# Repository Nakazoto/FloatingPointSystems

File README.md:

# Floating Point Systems

A repository for gathering documentation and understanding Floating-Point-Systems machines.

> [!NOTE]
> This documentation is incomplete and will be expanded as more information becomes available.

> [!WARNING]
> This README needs to be verified by the REPO owner: Nakazoto. 

## Overview

This project contains datasheets, documentation, and code related to floating-point-sytems machines.

## Index - For README

1. [Overview](#overview) - Reason What this REPO is for. 
2. [Contents](#contents---of-each-folder) - What is in the Folders.
3. [Index for FPS](#index---for-the-folders) - Folder links.
4. [Contributing](#contributing) - Things to look out for.
    - [Guide on Contributing](#a-little-guide) - A guide on contributing.

## Contents - Of each folder

- Documentation on floating-point-systems
- Some Datasheets
- Photos of Cards, etc
- Code for the Machines

## Index - For the folders

1. 	[OLD](!Old/) - Folder with old stuff , _A trade of some sort_
2. 	[AP 120B](AP%20120B/) - Documentation folder for AP 120B, _the predecessor of the FPS 100._
3. 	[FPS 100](FPS%20100/) - Documentation folder for FPS 100, _the successor of the AP 120B. With reduced cards._
4.	[FPS 164](FPS%20164/) - Documentation folder for FPS 164, _the favorite machine of Usagi Electric._
5. 	[FPS 3000](FPS%203000/) - Documentation folder for FPS 3000, _the machine of which only 1 still known to exist. And is almost the same as the XP 32 is._
6.	[FPS 5000](FPS%205000/) - Documentation folder for FPS 5000, _As mentioned in fps.pdf, this is a family of the AP 120B, just like any other machine._
7. 	[Random FPS information](Z.%20Others/) - Documetation folder for FPS information, _Like part prices and boardrevisions._
8. 	[Random PDFs](Z_Brochures/) - Documentation folder for PDFs, _Like product pages and folders._
9. 	[Boards in FPS Machines](Cully_Dave.txt) - Documentation file for cards, _The card configuration on different machines._
10. [Magazine of some sort](Digital_Design_V12_N06_198206.pdf) - Some sort of Magazine.
11. [Boards](FPS%20Board%20List.txt) - A board series, _with documentation._
12. [Known Surviving](KnownSurviving.txt) - Documentation file for Surviving machines, _With name, place, condition and maybe price ;D_
13. [Want to make a FPS?](NewFPSLayout.txt) - Documentation file for A Complete Card set for AP 120B, _And what cards some people have._

## Contributing

> [!CAUTION]
> This REPO is not meant for harassment, hating or any kind of destroying other people's work! So if you can help this repo grow, it is appreciated!

### A little guide:

> [!NOTE]
> _There are tons and tons of guides online that explain this in high detail. So look online!_ 

1. Create a Fork.
2. Import / Create the file you wanted to contribute in your own Fork.
3. Create a Pull request and explain what you changed.
	- You may have to add you fork (sometimes it does this automatically!)
4. Wait for a response!

> [!TIP]
> Here some links for videos:

 - [LINK for Guide](https://docs.github.com/en/pull-requests/collaborating-with-pull-requests/proposing-changes-to-your-work-with-pull-requests/creating-a-pull-request)
	- The NOTE you see applies in this case!

> [!IMPORTANT]
> To to achieve your goal it needs to be relevant to the REPO and it's subject.

<!--
NOTE:
INDEX-LINKS DO NOT WORK IN EDITOR,
this also is not done!
--!>

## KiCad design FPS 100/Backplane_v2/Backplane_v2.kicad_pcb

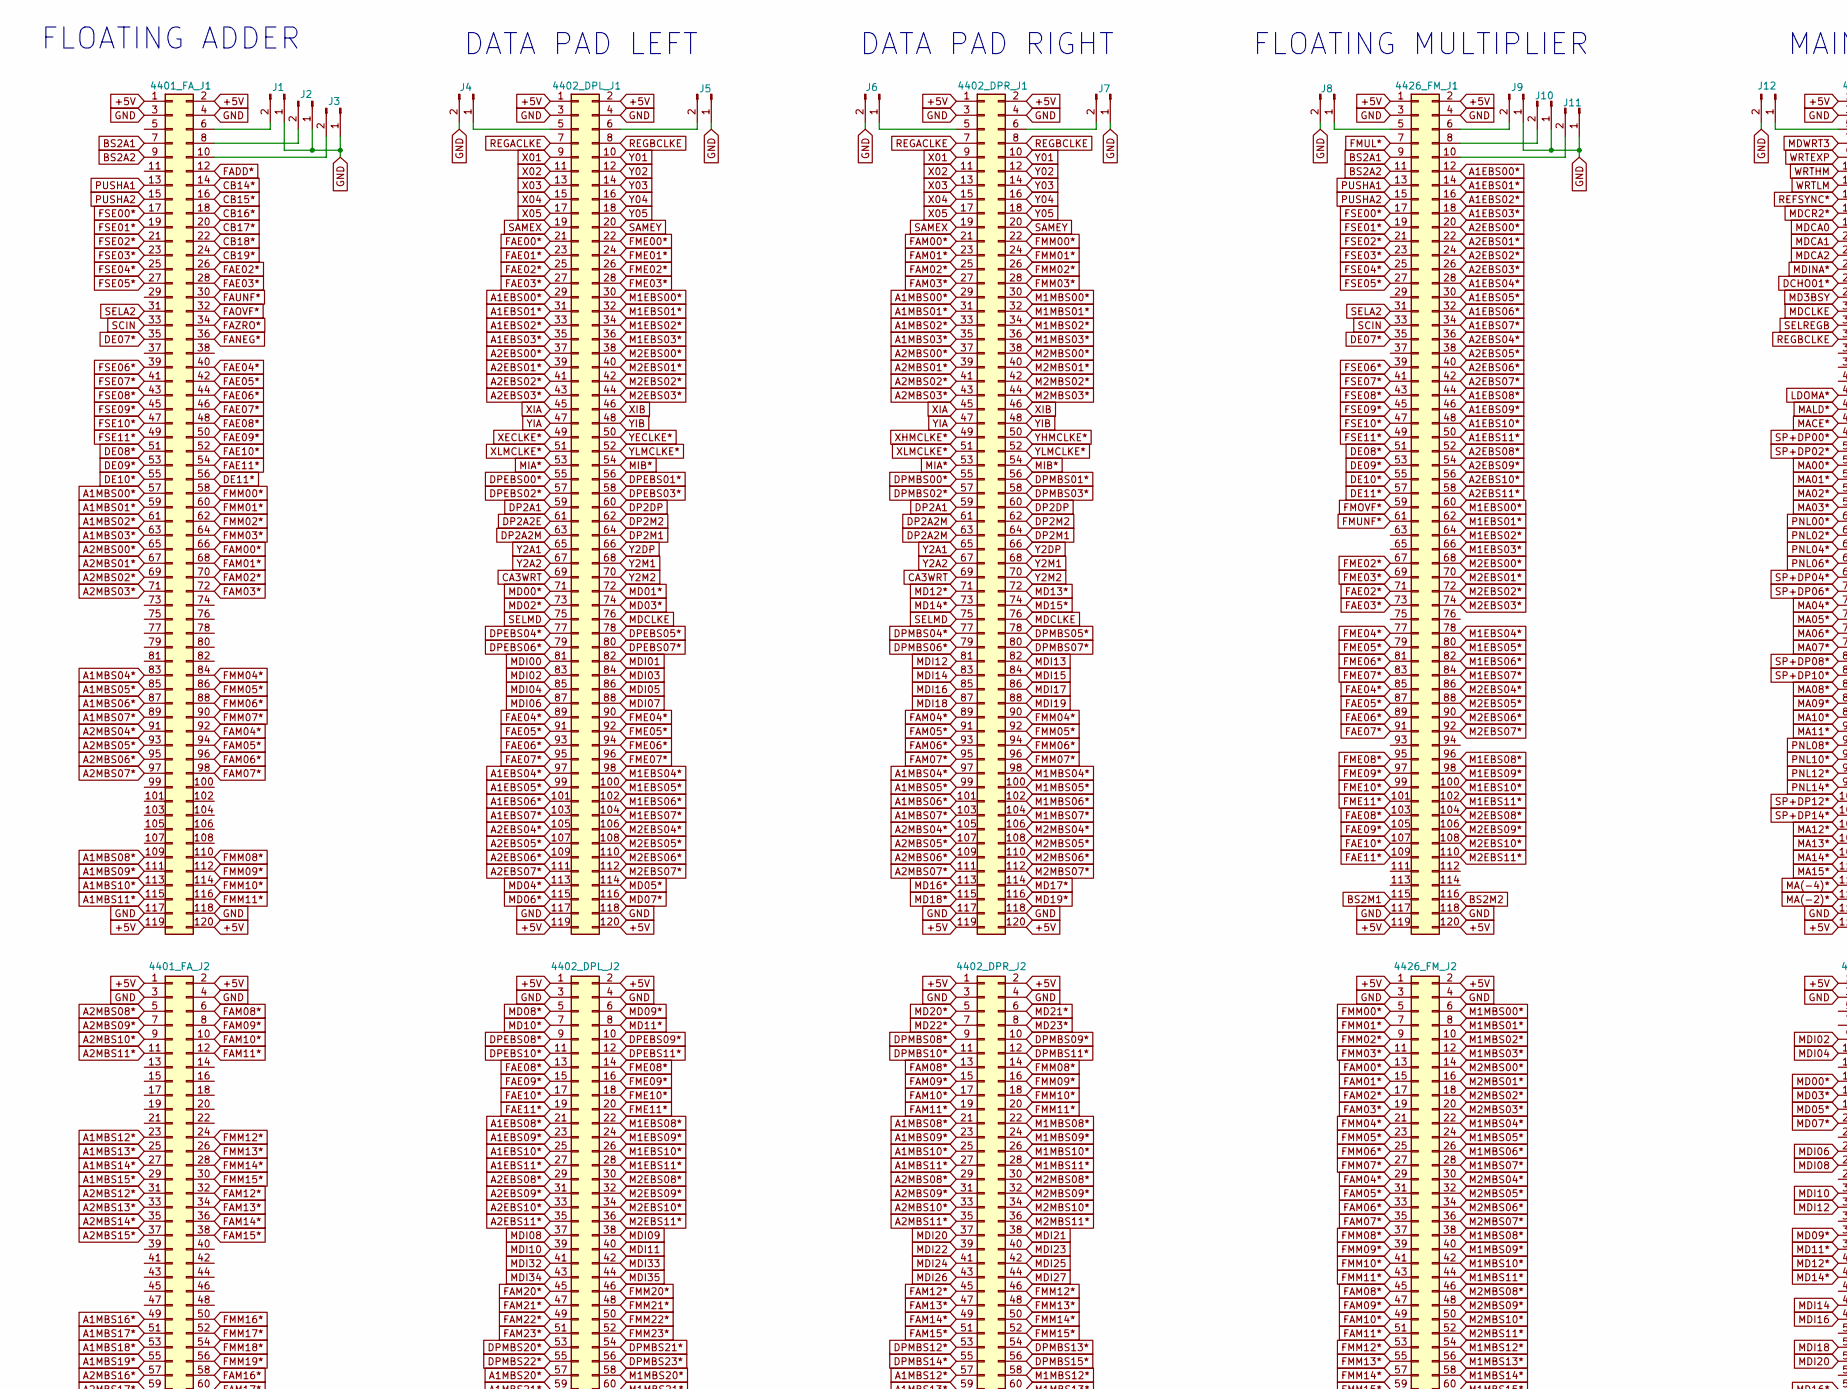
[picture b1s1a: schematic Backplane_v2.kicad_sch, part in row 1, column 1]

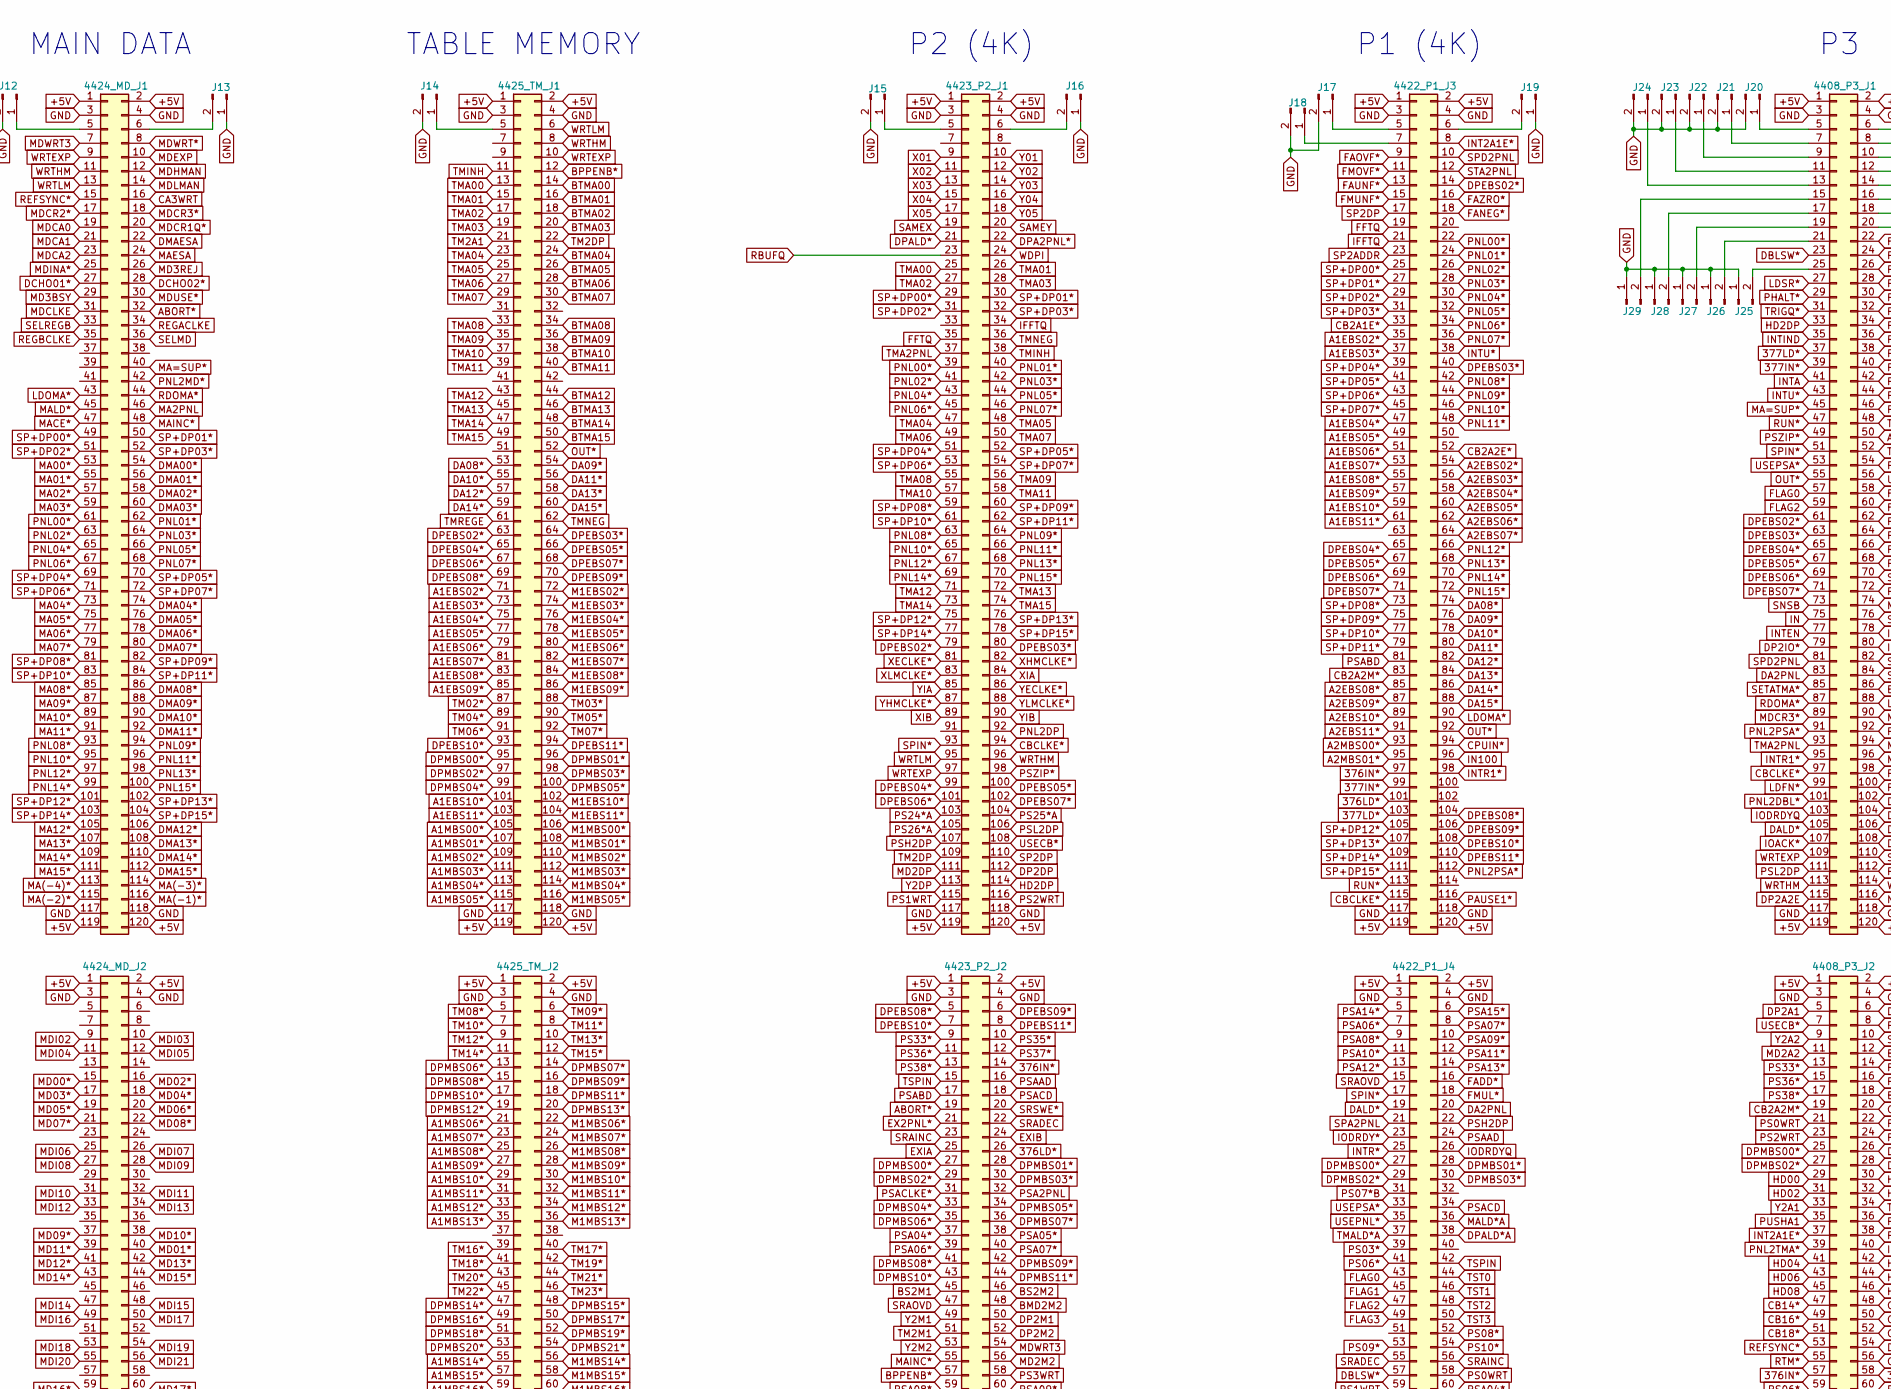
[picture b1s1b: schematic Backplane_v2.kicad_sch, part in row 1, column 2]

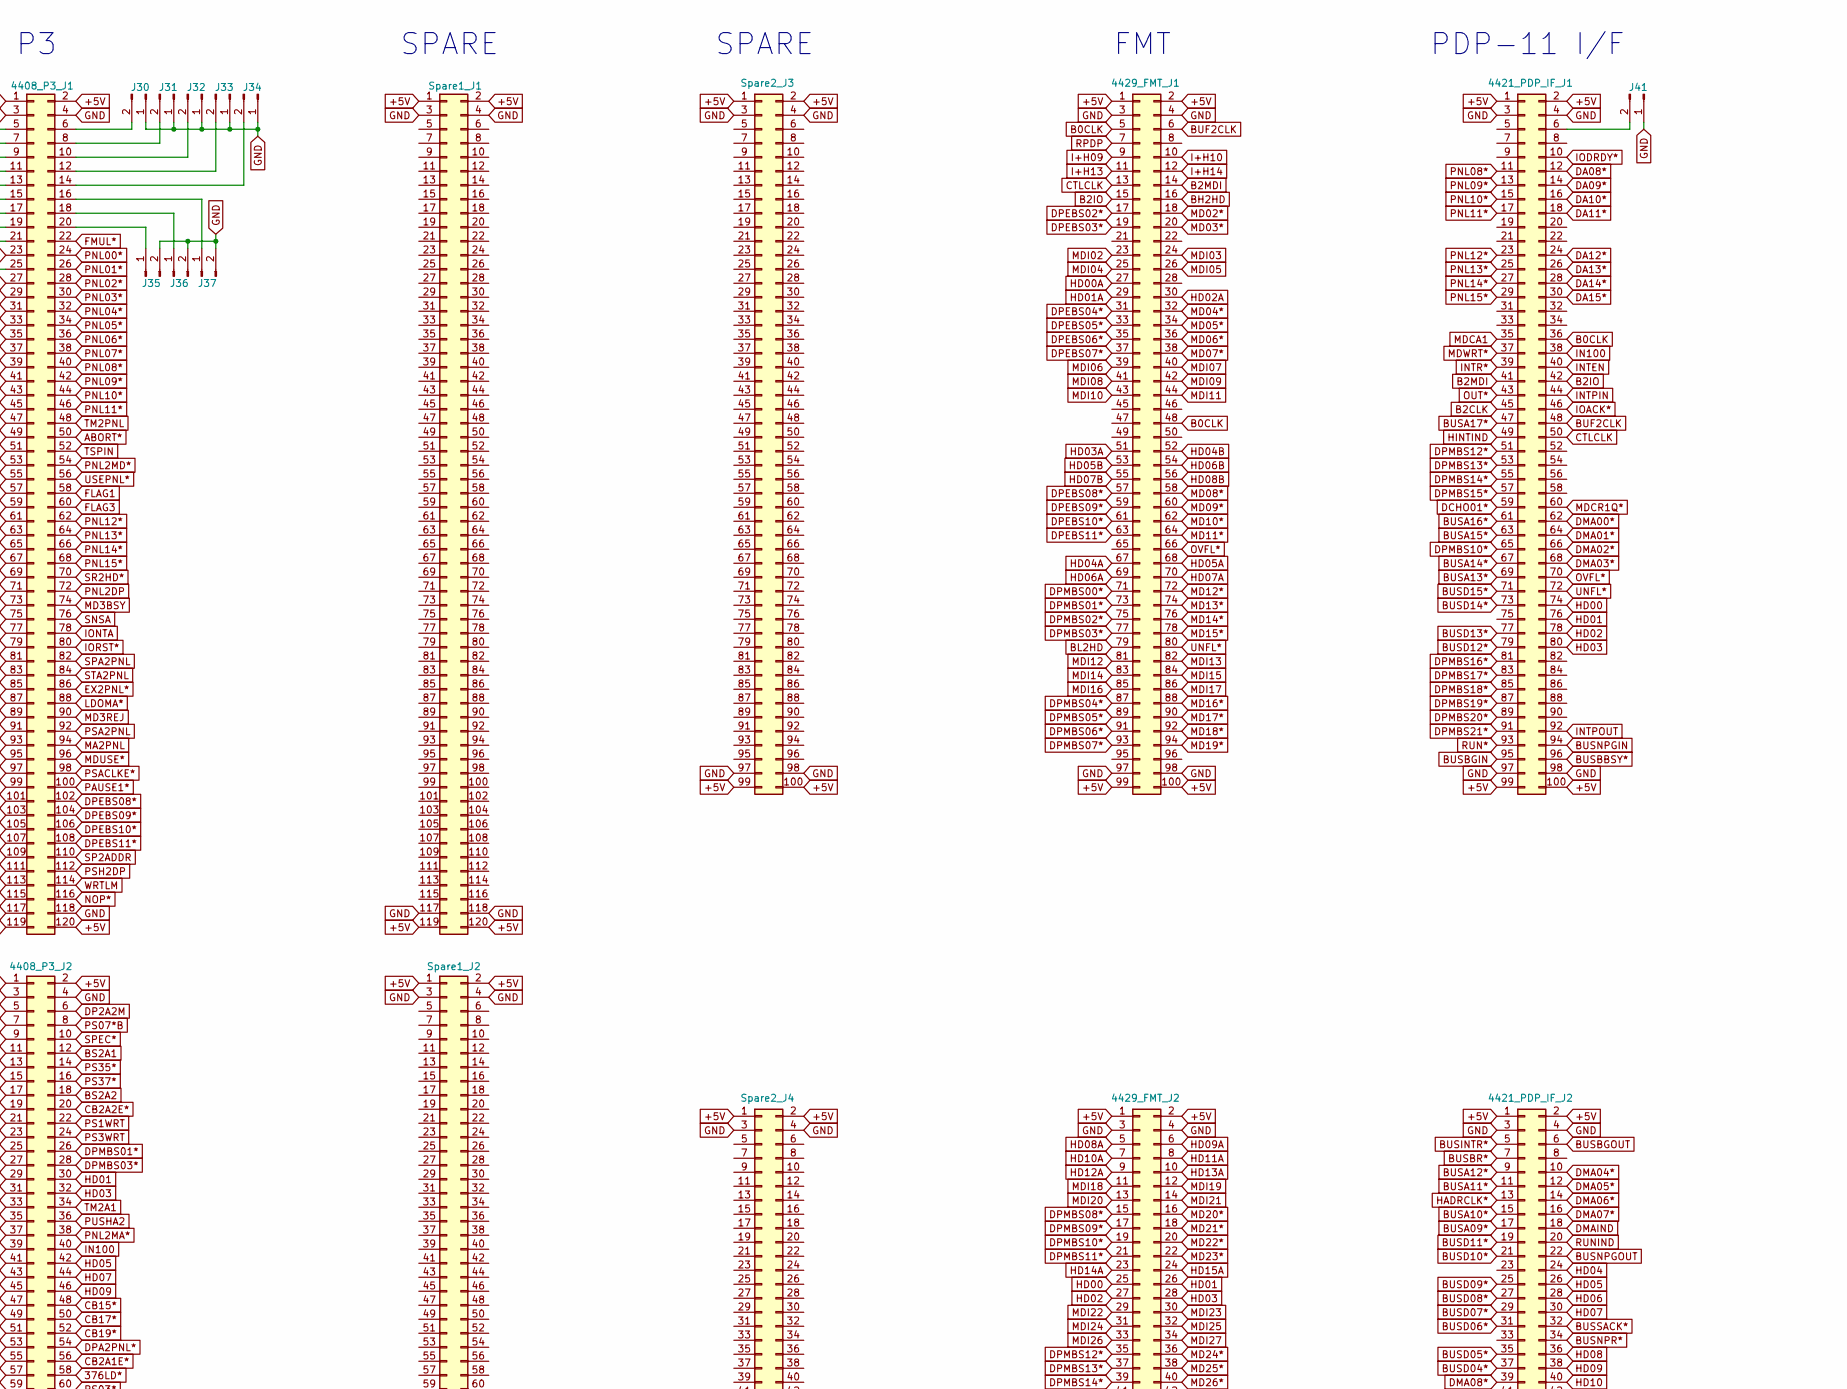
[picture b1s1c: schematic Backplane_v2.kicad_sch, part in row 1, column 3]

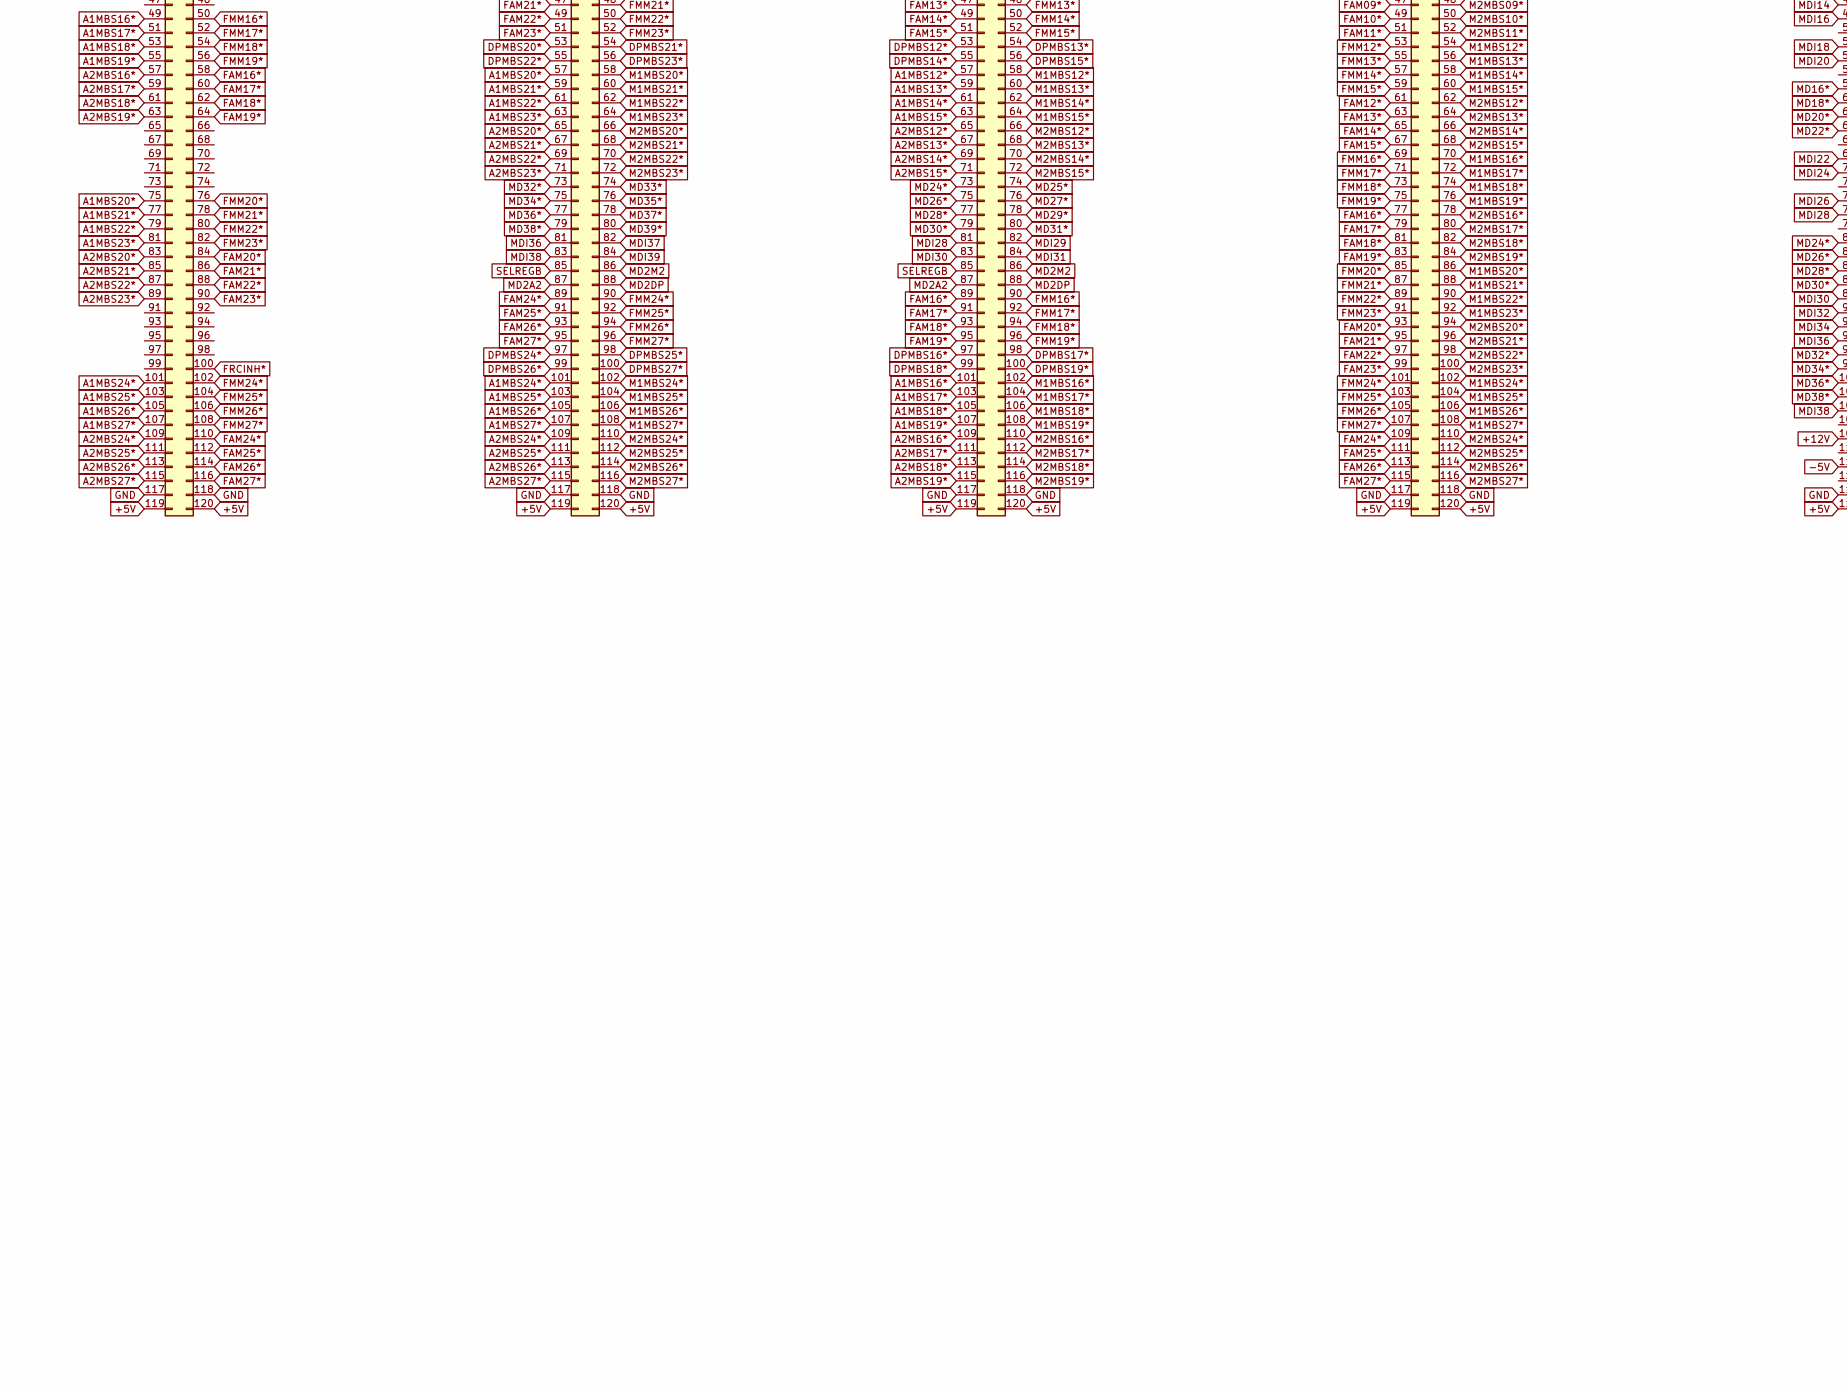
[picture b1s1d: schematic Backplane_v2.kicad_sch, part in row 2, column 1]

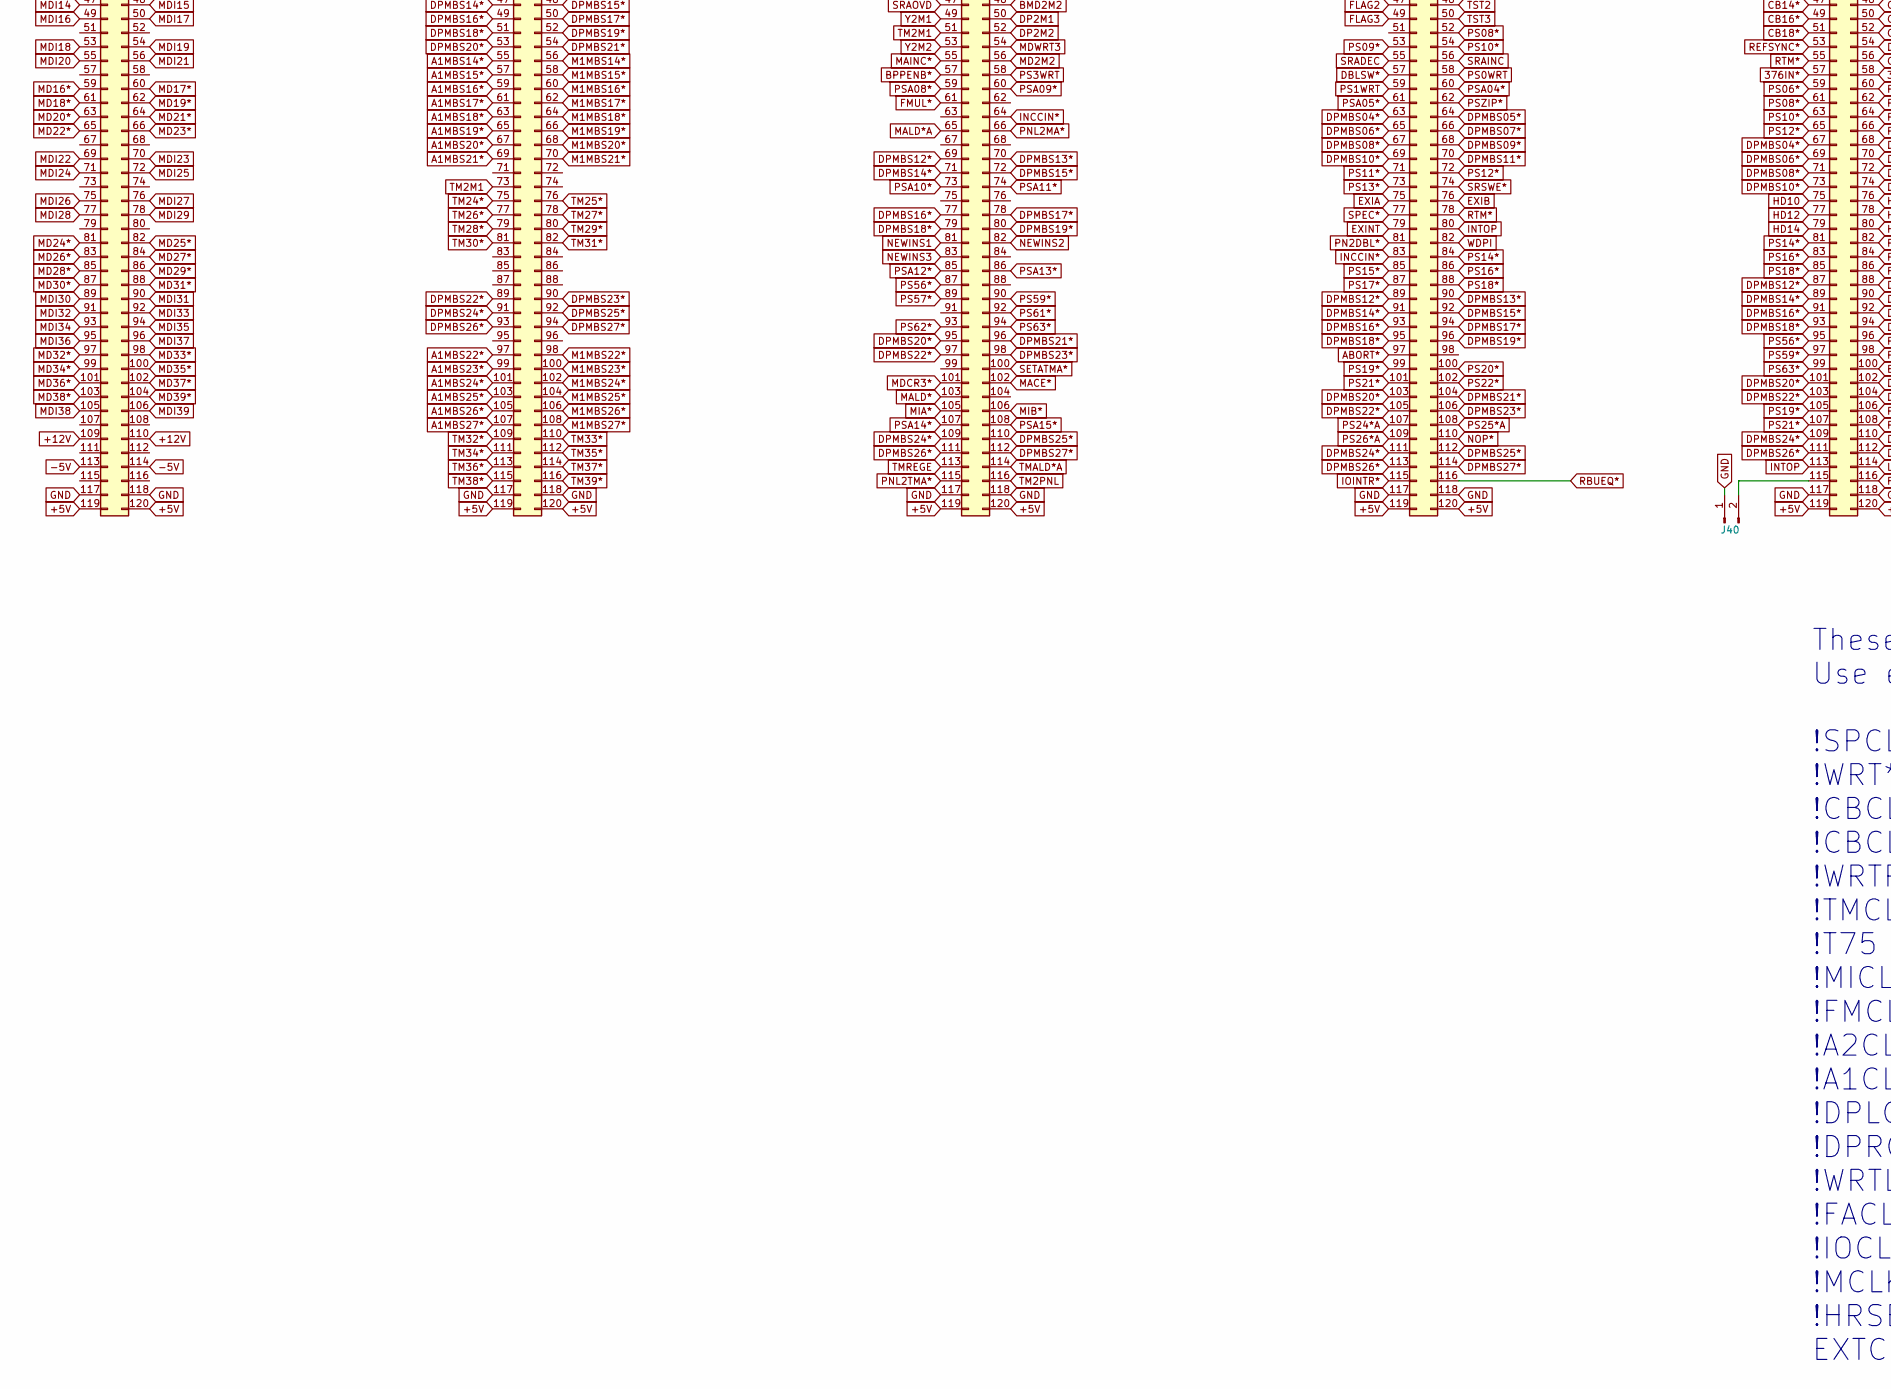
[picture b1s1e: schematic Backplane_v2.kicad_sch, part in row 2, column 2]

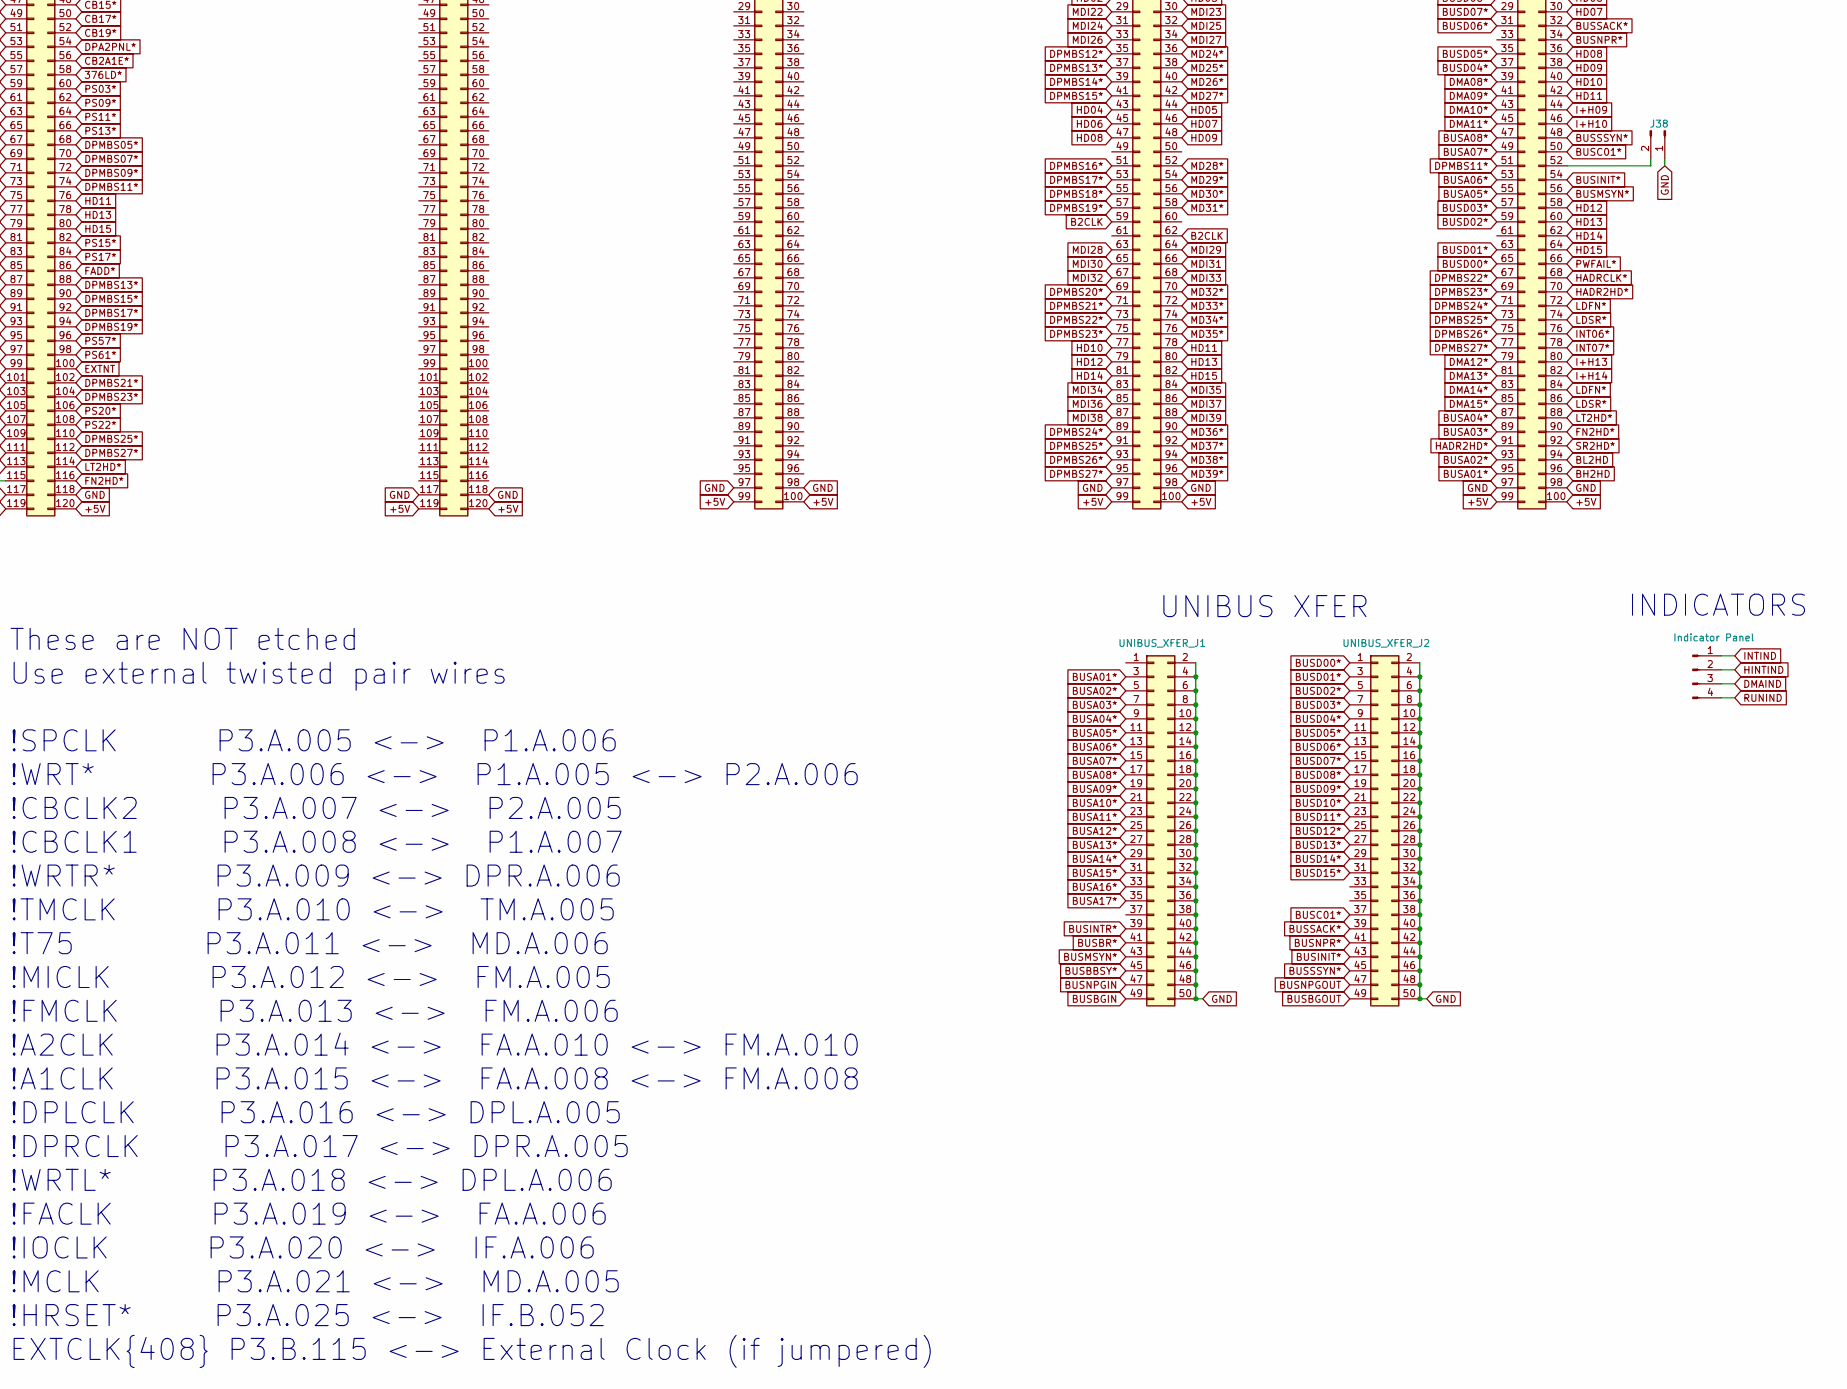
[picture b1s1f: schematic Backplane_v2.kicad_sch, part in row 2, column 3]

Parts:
4401_FA_J1, 4401_FA_J2, 4402_DPL_J1, 4402_DPL_J2, 4402_DPR_J1, 4402_DPR_J2, 4408_P3_J1, 4408_P3_J2, 4422_P1_J3, 4422_P1_J4, 4423_P2_J1, 4423_P2_J2, 4424_MD_J1, 4424_MD_J2, 4425_TM_J1, 4425_TM_J2, 4426_FM_J1, 4426_FM_J2: Conn_02x60_120pin; 120pin_Edge_Connector
4421_PDP_IF_J1, 4421_PDP_IF_J2, 4429_FMT_J1, 4429_FMT_J2: Conn_02x50_100pin; 100pin_Edge_Connector
J1, J2, J3, J4, J6, J7, J8, J9, J10, J11, J12, J13, J14, J15, J16, J17, J18, J19, J20, J21, J22, J23, J24, J25, J26, J27, J28, J29, J30, J31, J32, J33, J34, J35, J36, J37, J38, J40, J41: Conn_01x02_Pin; TwistedPairHeader
J5: TwistedPairHeader
J39: Indicator Panel; PinHeader_1x04_P2.54mm_Vertical
Spare1_J1, Spare1_J2: Conn_02x60_120pin; 120pin_Edge_Connector
Spare2_J3, Spare2_J4: Conn_02x50_100pin; 100pin_Edge_Connector
UNIBUS_XFER_J1, UNIBUS_XFER_J2: Conn_02x25_Odd_Even; PinHeader_2x25_P2.54mm_Vertical

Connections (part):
376IN*: 4408_P3_J2.57, 4422_P1_J3.97, 4423_P2_J2.14
376LD*: 4408_P3_J2.58, 4422_P1_J3.101, 4423_P2_J2.26
377IN*: 4408_P3_J1.39, 4422_P1_J3.99
377LD*: 4408_P3_J1.37, 4422_P1_J3.103
+5V: 4401_FA_J1.1, 4401_FA_J1.2, 4401_FA_J1.119, 4401_FA_J1.120, 4401_FA_J2.1, 4401_FA_J2.2, 4401_FA_J2.119, 4401_FA_J2.120, 4402_DPL_J1.1, 4402_DPL_J1.2, 4402_DPL_J1.119, 4402_DPL_J1.120, 4402_DPL_J2.1, 4402_DPL_J2.2, 4402_DPL_J2.119, 4402_DPL_J2.120, 4402_DPR_J1.1, 4402_DPR_J1.2, 4402_DPR_J1.119, 4402_DPR_J1.120, 4402_DPR_J2.1, 4402_DPR_J2.2, 4402_DPR_J2.119, 4402_DPR_J2.120, 4408_P3_J1.1, 4408_P3_J1.2, 4408_P3_J1.119, 4408_P3_J1.120, 4408_P3_J2.1, 4408_P3_J2.2, 4408_P3_J2.119, 4408_P3_J2.120, 4421_PDP_IF_J1.1, 4421_PDP_IF_J1.2, 4421_PDP_IF_J1.99, 4421_PDP_IF_J1.100, 4421_PDP_IF_J2.1, 4421_PDP_IF_J2.2, 4421_PDP_IF_J2.99, 4421_PDP_IF_J2.100, 4422_P1_J3.1, 4422_P1_J3.2, 4422_P1_J3.119, 4422_P1_J3.120, 4422_P1_J4.1, 4422_P1_J4.2, 4422_P1_J4.119, 4422_P1_J4.120, 4423_P2_J1.1, 4423_P2_J1.2, 4423_P2_J1.119, 4423_P2_J1.120, 4423_P2_J2.1, 4423_P2_J2.2, 4423_P2_J2.119, 4423_P2_J2.120, 4424_MD_J1.1, 4424_MD_J1.2, 4424_MD_J1.119, 4424_MD_J1.120, 4424_MD_J2.1, 4424_MD_J2.2, 4424_MD_J2.119, 4424_MD_J2.120, 4425_TM_J1.1, 4425_TM_J1.2, 4425_TM_J1.119, 4425_TM_J1.120, 4425_TM_J2.1, 4425_TM_J2.2, 4425_TM_J2.119, 4425_TM_J2.120, 4426_FM_J1.1, 4426_FM_J1.2, 4426_FM_J1.119, 4426_FM_J1.120, 4426_FM_J2.1, 4426_FM_J2.2, 4426_FM_J2.119, 4426_FM_J2.120, 4429_FMT_J1.1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
+12V: 4424_MD_J2.109, 4424_MD_J2.110
-5V: 4424_MD_J2.113, 4424_MD_J2.114
A1EBS00*: 4402_DPL_J1.29, 4426_FM_J1.12
A1EBS01*: 4402_DPL_J1.31, 4426_FM_J1.14
A1EBS02*: 4402_DPL_J1.33, 4422_P1_J3.35, 4425_TM_J1.71, 4426_FM_J1.16
A1EBS03*: 4402_DPL_J1.35, 4422_P1_J3.37, 4425_TM_J1.73, 4426_FM_J1.18
A1EBS04*: 4402_DPL_J1.97, 4422_P1_J3.47, 4425_TM_J1.75, 4426_FM_J1.28
A1EBS05*: 4402_DPL_J1.99, 4422_P1_J3.49, 4425_TM_J1.77, 4426_FM_J1.30
A1EBS06*: 4402_DPL_J1.101, 4422_P1_J3.51, 4425_TM_J1.79, 4426_FM_J1.32
A1EBS07*: 4402_DPL_J1.103, 4422_P1_J3.53, 4425_TM_J1.81, 4426_FM_J1.34
A1EBS08*: 4402_DPL_J2.21, 4422_P1_J3.55, 4425_TM_J1.83, 4426_FM_J1.44
A1EBS09*: 4402_DPL_J2.23, 4422_P1_J3.57, 4425_TM_J1.85, 4426_FM_J1.46
A1EBS10*: 4402_DPL_J2.25, 4422_P1_J3.59, 4425_TM_J1.101, 4426_FM_J1.48
A1EBS11*: 4402_DPL_J2.27, 4422_P1_J3.61, 4425_TM_J1.103, 4426_FM_J1.50
A1MBS00*: 4401_FA_J1.57, 4402_DPR_J1.29, 4425_TM_J1.105
A1MBS01*: 4401_FA_J1.59, 4402_DPR_J1.31, 4425_TM_J1.107
A1MBS02*: 4401_FA_J1.61, 4402_DPR_J1.33, 4425_TM_J1.109
A1MBS03*: 4401_FA_J1.63, 4402_DPR_J1.35, 4425_TM_J1.111
A1MBS04*: 4401_FA_J1.83, 4402_DPR_J1.97, 4425_TM_J1.113
A1MBS05*: 4401_FA_J1.85, 4402_DPR_J1.99, 4425_TM_J1.115
A1MBS06*: 4401_FA_J1.87, 4402_DPR_J1.101, 4425_TM_J2.21
A1MBS07*: 4401_FA_J1.89, 4402_DPR_J1.103, 4425_TM_J2.23
A1MBS08*: 4401_FA_J1.109, 4402_DPR_J2.21, 4425_TM_J2.25
A1MBS09*: 4401_FA_J1.111, 4402_DPR_J2.23, 4425_TM_J2.27
A1MBS10*: 4401_FA_J1.113, 4402_DPR_J2.25, 4425_TM_J2.29
A1MBS11*: 4401_FA_J1.115, 4402_DPR_J2.27, 4425_TM_J2.31
A1MBS12*: 4401_FA_J2.23, 4402_DPR_J2.57, 4425_TM_J2.33
A1MBS13*: 4401_FA_J2.25, 4402_DPR_J2.59, 4425_TM_J2.35
A1MBS14*: 4401_FA_J2.27, 4402_DPR_J2.61, 4425_TM_J2.55
A1MBS15*: 4401_FA_J2.29, 4402_DPR_J2.63, 4425_TM_J2.57
A1MBS16*: 4401_FA_J2.49, 4402_DPR_J2.101, 4425_TM_J2.59
A1MBS17*: 4401_FA_J2.51, 4402_DPR_J2.103, 4425_TM_J2.61
A1MBS18*: 4401_FA_J2.53, 4402_DPR_J2.105, 4425_TM_J2.63
A1MBS19*: 4401_FA_J2.55, 4402_DPR_J2.107, 4425_TM_J2.65
A1MBS20*: 4401_FA_J2.75, 4402_DPL_J2.57, 4425_TM_J2.67
A1MBS21*: 4401_FA_J2.77, 4402_DPL_J2.59, 4425_TM_J2.69
A1MBS22*: 4401_FA_J2.79, 4402_DPL_J2.61, 4425_TM_J2.97
A1MBS23*: 4401_FA_J2.81, 4402_DPL_J2.63, 4425_TM_J2.99
A1MBS24*: 4401_FA_J2.101, 4402_DPL_J2.101, 4425_TM_J2.101
A1MBS25*: 4401_FA_J2.103, 4402_DPL_J2.103, 4425_TM_J2.103
A1MBS26*: 4401_FA_J2.105, 4402_DPL_J2.105, 4425_TM_J2.105
A1MBS27*: 4401_FA_J2.107, 4402_DPL_J2.107, 4425_TM_J2.107
A2EBS00*: 4402_DPL_J1.37, 4426_FM_J1.20
A2EBS01*: 4402_DPL_J1.39, 4426_FM_J1.22
A2EBS02*: 4402_DPL_J1.41, 4422_P1_J3.54, 4426_FM_J1.24
A2EBS03*: 4402_DPL_J1.43, 4422_P1_J3.56, 4426_FM_J1.26
A2EBS04*: 4402_DPL_J1.105, 4422_P1_J3.58, 4426_FM_J1.36
A2EBS05*: 4402_DPL_J1.107, 4422_P1_J3.60, 4426_FM_J1.38
A2EBS06*: 4402_DPL_J1.109, 4422_P1_J3.62, 4426_FM_J1.40
A2EBS07*: 4402_DPL_J1.111, 4422_P1_J3.64, 4426_FM_J1.42
A2EBS08*: 4402_DPL_J2.29, 4422_P1_J3.85, 4426_FM_J1.52
A2EBS09*: 4402_DPL_J2.31, 4422_P1_J3.87, 4426_FM_J1.54
A2EBS10*: 4402_DPL_J2.33, 4422_P1_J3.89, 4426_FM_J1.56
A2EBS11*: 4402_DPL_J2.35, 4422_P1_J3.91, 4426_FM_J1.58
A2MBS00*: 4401_FA_J1.65, 4402_DPR_J1.37, 4422_P1_J3.93
A2MBS01*: 4401_FA_J1.67, 4402_DPR_J1.39, 4422_P1_J3.95
A2MBS02*: 4401_FA_J1.69, 4402_DPR_J1.41
A2MBS03*: 4401_FA_J1.71, 4402_DPR_J1.43
A2MBS04*: 4401_FA_J1.91, 4402_DPR_J1.105
A2MBS05*: 4401_FA_J1.93, 4402_DPR_J1.107
A2MBS06*: 4401_FA_J1.95, 4402_DPR_J1.109
A2MBS07*: 4401_FA_J1.97, 4402_DPR_J1.111
A2MBS08*: 4401_FA_J2.5, 4402_DPR_J2.29
A2MBS09*: 4401_FA_J2.7, 4402_DPR_J2.31
A2MBS10*: 4401_FA_J2.9, 4402_DPR_J2.33
A2MBS11*: 4401_FA_J2.11, 4402_DPR_J2.35
A2MBS12*: 4401_FA_J2.31, 4402_DPR_J2.65
A2MBS13*: 4401_FA_J2.33, 4402_DPR_J2.67
A2MBS14*: 4401_FA_J2.35, 4402_DPR_J2.69
A2MBS15*: 4401_FA_J2.37, 4402_DPR_J2.71
A2MBS16*: 4401_FA_J2.57, 4402_DPR_J2.109
A2MBS17*: 4401_FA_J2.59, 4402_DPR_J2.111
A2MBS18*: 4401_FA_J2.61, 4402_DPR_J2.113
A2MBS19*: 4401_FA_J2.63, 4402_DPR_J2.115
A2MBS20*: 4401_FA_J2.83, 4402_DPL_J2.65
A2MBS21*: 4401_FA_J2.85, 4402_DPL_J2.67
A2MBS22*: 4401_FA_J2.87, 4402_DPL_J2.69
A2MBS23*: 4401_FA_J2.89, 4402_DPL_J2.71
A2MBS24*: 4401_FA_J2.109, 4402_DPL_J2.109
A2MBS25*: 4401_FA_J2.111, 4402_DPL_J2.111
A2MBS26*: 4401_FA_J2.113, 4402_DPL_J2.113
A2MBS27*: 4401_FA_J2.115, 4402_DPL_J2.115
ABORT*: 4408_P3_J1.50, 4422_P1_J4.97, 4423_P2_J2.19, 4424_MD_J1.32
B0CLK: 4421_PDP_IF_J1.36, 4429_FMT_J1.5, 4429_FMT_J1.48
B2CLK: 4421_PDP_IF_J1.45, 4429_FMT_J2.59, 4429_FMT_J2.62
B2IO: 4421_PDP_IF_J1.42, 4429_FMT_J1.15
B2MDI: 4421_PDP_IF_J1.41, 4429_FMT_J1.14
BH2HD: 4421_PDP_IF_J2.96, 4429_FMT_J1.16
BL2HD: 4421_PDP_IF_J2.94, 4429_FMT_J1.79
BMD2M2: 4423_P2_J2.48
BPPENB*: 4423_P2_J2.57, 4425_TM_J1.12
BS2A1: 4401_FA_J1.7, 4408_P3_J2.12, 4426_FM_J1.9
BS2A2: 4401_FA_J1.9, 4408_P3_J2.18, 4426_FM_J1.11
BS2M1: 4423_P2_J2.45, 4426_FM_J1.115
BS2M2: 4423_P2_J2.46, 4426_FM_J1.116
BTMA00: 4425_TM_J1.14
BTMA01: 4425_TM_J1.16
BTMA02: 4425_TM_J1.18
BTMA03: 4425_TM_J1.20
BTMA04: 4425_TM_J1.24
BTMA05: 4425_TM_J1.26
BTMA06: 4425_TM_J1.28
BTMA07: 4425_TM_J1.30
BTMA08: 4425_TM_J1.34
BTMA09: 4425_TM_J1.36
BTMA10: 4425_TM_J1.38
BTMA11: 4425_TM_J1.40
BTMA12: 4425_TM_J1.44
BTMA13: 4425_TM_J1.46
BTMA14: 4425_TM_J1.48
BTMA15: 4425_TM_J1.50
BUF2CLK: 4421_PDP_IF_J1.48, 4429_FMT_J1.6
BUSA01*: 4421_PDP_IF_J2.95, UNIBUS_XFER_J1.3
BUSA02*: 4421_PDP_IF_J2.93, UNIBUS_XFER_J1.5
BUSA03*: 4421_PDP_IF_J2.89, UNIBUS_XFER_J1.7
BUSA04*: 4421_PDP_IF_J2.87, UNIBUS_XFER_J1.9
BUSA05*: 4421_PDP_IF_J2.55, UNIBUS_XFER_J1.11
BUSA06*: 4421_PDP_IF_J2.53, UNIBUS_XFER_J1.13
BUSA07*: 4421_PDP_IF_J2.49, UNIBUS_XFER_J1.15
BUSA08*: 4421_PDP_IF_J2.47, UNIBUS_XFER_J1.17
BUSA09*: 4421_PDP_IF_J2.17, UNIBUS_XFER_J1.19
BUSA10*: 4421_PDP_IF_J2.15, UNIBUS_XFER_J1.21
BUSA11*: 4421_PDP_IF_J2.11, UNIBUS_XFER_J1.23
BUSA12*: 4421_PDP_IF_J2.9, UNIBUS_XFER_J1.25
BUSA13*: 4421_PDP_IF_J1.69, UNIBUS_XFER_J1.27
BUSA14*: 4421_PDP_IF_J1.67, UNIBUS_XFER_J1.29
BUSA15*: 4421_PDP_IF_J1.63, UNIBUS_XFER_J1.31
BUSA16*: 4421_PDP_IF_J1.61, UNIBUS_XFER_J1.33
BUSA17*: 4421_PDP_IF_J1.47, UNIBUS_XFER_J1.35
BUSBBSY*: 4421_PDP_IF_J1.96, UNIBUS_XFER_J1.45
BUSBGIN: 4421_PDP_IF_J1.95, UNIBUS_XFER_J1.49
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
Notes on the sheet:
P2 (4K)
FLOATING MULTIPLIER
PDP-11 I/F
FLOATING ADDER
FMT
DATA PAD RIGHT
UNIBUS XFER
SPARE
MAIN DATA
INDICATORS
These are NOT etched Use external twisted pair wires !SPCLK P3.A.005 <-> P1.A.006 !WRT* P3.A.006 <-> P1.A.005 <-> P2.A.006 !CBCLK2 P3.A.007 <-> P2.A.005 !CBCLK1 P3.A.008 <-> P1.A.007 !WRTR* P3.A.009 <-> DPR.A.006 !TMCLK P3.A.010 <-> TM.A.005 !T75 P3.A.011 <-> MD.A.006 !MICLK P3.A.012 <-> FM.A.005 !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
P1 (4K)
DATA PAD LEFT
TABLE MEMORY

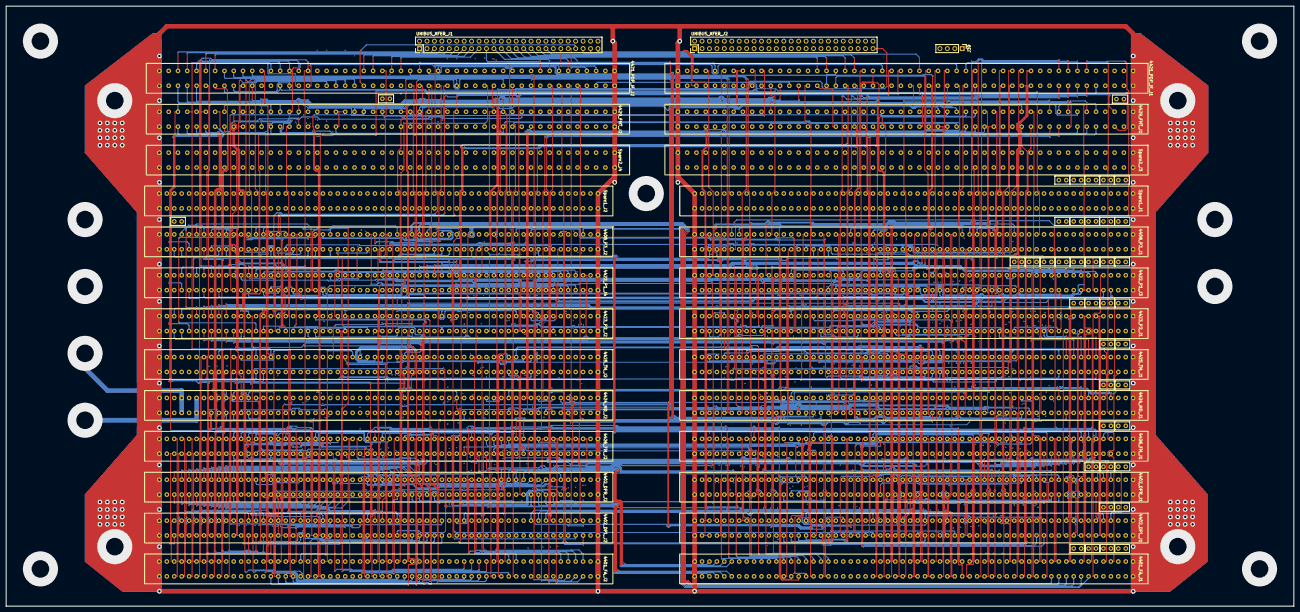
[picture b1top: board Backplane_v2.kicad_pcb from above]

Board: 6 copper layers, 440.0 x 205.0 mm, 69 parts (0 on the bottom side), 785 nets.

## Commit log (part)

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2025-06-11 2025/6/11
2026-01-09 2026/1/9
2026-01-10 2026/1/10
2026-01-12 2026/1/12
2026-01-13 2026/1/13
2026-01-16 2026/1/15
2026-01-19 2026/1/18
2026-01-19 2026/1/19
2026-01-20 2026/1/20
2026-01-21 2026/1/21
2026-01-23 2025/1/22
2026-01-26 2026/1/26
2026-02-11 2026/2/10
2026-03-03 2026/3/3
